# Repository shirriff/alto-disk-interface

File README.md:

# A Diablo disk emulator for use with a Xerox Alto

Note: This is still under development and is not working yet

The concept is a small box that you can plug into the Alto's disk interface, replacing the Diablo disk. The box will emulate the disk drive,
using a disk image from a SD card.

The hardware design is in the interface directory. It is based on a Teensy 4.1 microcontroller and uses a LCD touch screen as the user interface.

The driver software is in the TestApp directory.

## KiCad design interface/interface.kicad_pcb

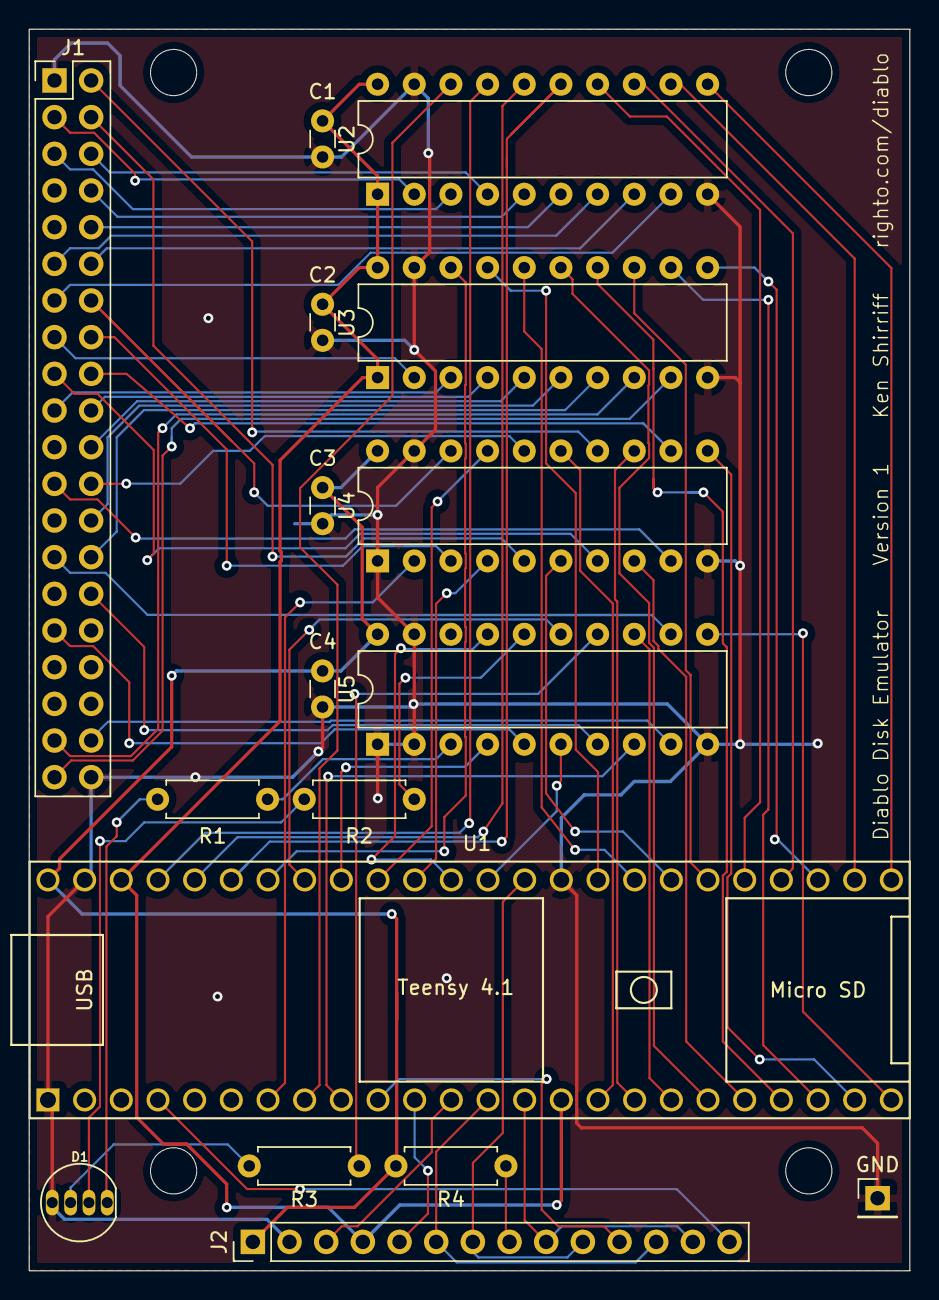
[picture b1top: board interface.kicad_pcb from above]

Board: 2 copper layers, 61.0 x 86.0 mm, 21 parts (0 on the bottom side), 76 nets.

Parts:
C1, C2, C3, C4: .1uF; C_Disc_D3.0mm_W1.6mm_P2.50mm
D1: LED_RGBC; LED-RGB-THRU
GND: TestPoint; Pin_Header_Straight_1x01_Pitch2.54mm
H1, H2, H3, H4: MountingHole; MountingHole_M3
J1: Conn_01x40_Female; connector-2x20
J2: Screen connector; Pin_Header_Straight_1x14_Pitch2.54mm
R1: 180; R_Axial_DIN0207_L6.3mm_D2.5mm_P7.62mm_Horizontal
R2, R3, R4: 100; R_Axial_DIN0207_L6.3mm_D2.5mm_P7.62mm_Horizontal
U1: Teensy4.1; Teensy41_simple
U2, U3: 74LVC245; DIP-20_W7.62mm
U4, U5: 74ACT240; DIP-20_W7.62mm

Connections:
/ADR_ACK: U1.39, U4.17
/CS: J2.3, U1.12
/CYL1: U1.42, U3.18
/CYL2: U1.44, U2.16
/CYL4: U1.33, U3.17
/CYL8: U1.22, U3.12
/CYL16: U1.29, U2.14
/CYL32: U1.25, U2.11
/CYL64: U1.43, U2.15
/CYL128: U1.26, U2.12
/DC: J2.5, U1.11
/DSK_ADR_ACK: J1.16, U4.3
/DSK_CYL1: J1.15, U3.2
/DSK_CYL2: J1.6, U2.4
/DSK_CYL4: J1.19, U3.3
/DSK_CYL8: J1.37, U3.8
/DSK_CYL16: J1.10, U2.6
/DSK_CYL32: J1.13, U2.9
/DSK_CYL64: J1.8, U2.5
/DSK_CYL128: J1.12, U2.8
/DSK_HEAD_SEL: J1.28, U3.7
/DSK_LAI: J1.18, U4.12
/DSK_RD_CLK: J1.2, U4.14
/DSK_RD_DATA: J1.38, U5.9
/DSK_RD_GATE: J1.39, U3.9
/DSK_READY: J1.31, U5.5
/DSK_RESTORE: J1.20, U3.4
/DSK_SECT1: J1.27, U5.12
/DSK_SECT2: J1.14, U4.18
/DSK_SECT4: J1.24, U4.16
/DSK_SECT8: J1.23, U4.9
/DSK_SECTOR: J1.30, U5.7
/DSK_SEEK_INCMP: J1.17, U4.7
/DSK_SEL1: J1.5, U2.3
/DSK_SEL4: J1.11, U2.7
/DSK_SRW: J1.4, U4.5
/DSK_STROBE: J1.22, U3.5
/DSK_WR_DATA: J1.3, U2.2
/DSK_WR_GATE: J1.26, U3.6
/GND: C1.2, C2.2, C3.2, C4.2, D1.4, GND.1, J1.1, J1.40, J2.2, U1.1, U1.34, U1.47, U2.10, U2.19, U3.10, U3.19, U4.1, U4.10, U4.19, U5.1, U5.2, U5.10, U5.19
/HEAD_SEL: U1.30, U3.13
/LAI: U1.20, U4.8
/LED: J2.8, R4.1
/LED_B: R3.2, U5.14
/LED_B_PWM: U1.36, U5.6
/LED_G: R2.2, U5.16
/LED_G_PWM: U1.40, U5.4
/LED_R: R1.2, U5.3
/LED_R_PWM: U1.37, U5.17
/RD_CLK: U1.31, U4.6
/RD_DATA: U1.24, U5.11
/RD_GATE: U1.27, U3.11
/READY: U1.41, U5.15
/RESTORE: U1.32, U3.16
/SCK: J2.7, J2.10, U1.35
/SDI: J2.6, J2.12, U1.13
/SDO: J2.9, J2.13, U1.14
/SECT1: U1.9, U5.8
/SECT2: U1.7, U4.2
/SECT4: U1.38, U4.4
/SECT8: U1.23, U4.11
/SECTOR: U1.18, U5.13
/SEEK_INCMP: U1.17, U4.13
/SEL1: U1.45, U2.17
/SEL4: U1.28, U2.13
/SRW: U1.16, U4.15
/STROBE: U1.19, U3.15
/T_CS: J2.11, U1.10
/T_IRQ: J2.14, U1.4
/VCC3: C1.1, C2.1, J2.4, U1.15, U1.46, U2.1, U2.20, U3.1, U3.20
/VCC5: C3.1, C4.1, J2.1, R4.2, U1.48, U4.20, U5.20
/WR_DATA: U1.8, U2.18
/WR_GATE: U1.21, U3.14
unnamed: D1.1, R1.1
unnamed: D1.2, R2.1
unnamed: D1.3, R3.1

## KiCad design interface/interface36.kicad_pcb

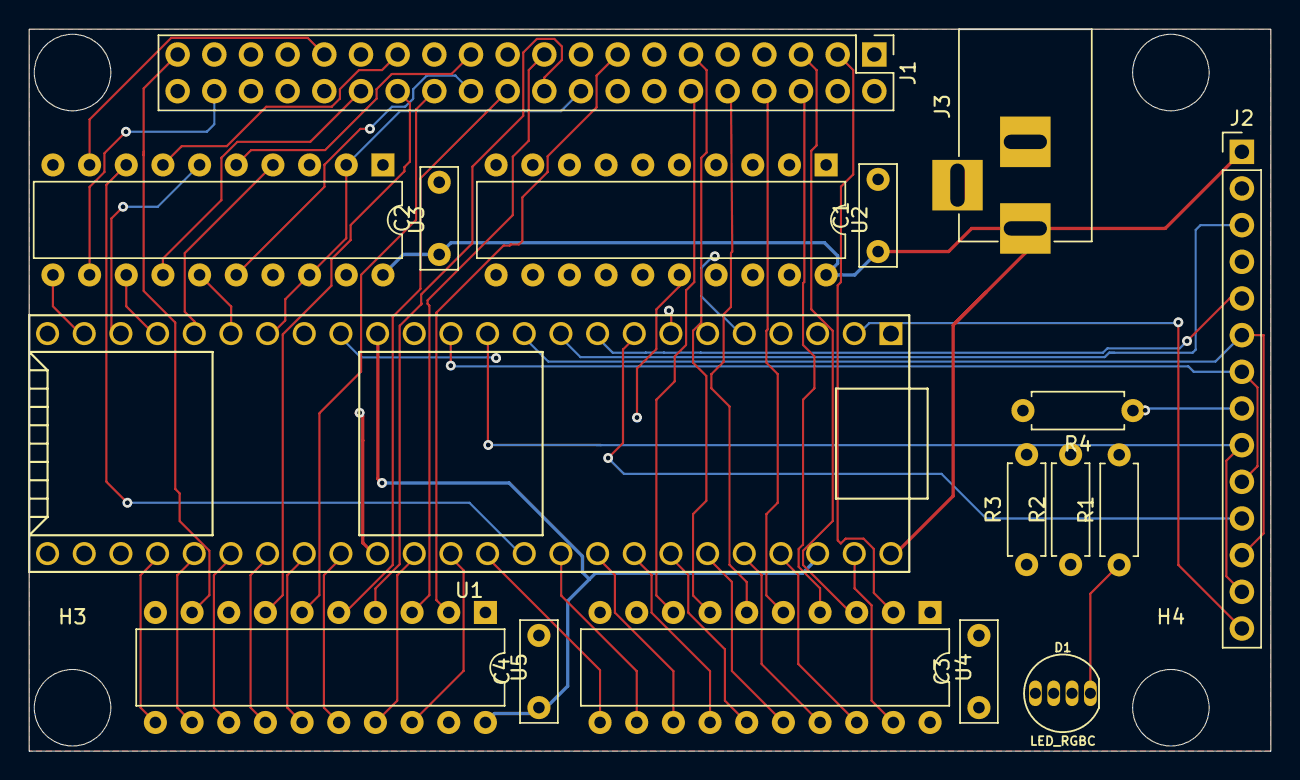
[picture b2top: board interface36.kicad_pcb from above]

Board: 2 copper layers, 86.0 x 50.0 mm, 21 parts (0 on the bottom side), 75 nets.

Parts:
C1, C2, C3, C4: .1uF; C_Rect_L7.0mm_W2.5mm_P5.00mm
D1: LED_RGBC; LED-RGB-THRU
H1, H2, H3, H4: MountingHole; MountingHole_5.3mm_M5
J1: Conn_01x40_Female; Pin_Header_Straight_2x20_Pitch2.54mm
J2: Conn_01x14_Female; Pin_Header_Straight_1x14_Pitch2.54mm
J3: Jack-DC; BARREL_JACK
R1: 180; R_Axial_DIN0207_L6.3mm_D2.5mm_P7.62mm_Horizontal
R2, R3, R4: 100; R_Axial_DIN0207_L6.3mm_D2.5mm_P7.62mm_Horizontal
U1: Teensy3.6; Teensy_36_simple
U2, U3: 74ACT240; DIP-20_W7.62mm
U4, U5: 74LVC245; DIP-20_W7.62mm

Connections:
/ADR_ACK: U1.16, U2.8
/CS: J2.3, U1.10
/CYL1: U1.39, U4.12
/CYL2: U1.42, U4.15
/CYL3: U1.37, U4.11
/CYL4: U1.41, U4.14
/CYL5: U1.29, U5.12
/CYL6: U1.35, U5.17
/CYL7: U1.43, U4.16
/CYL8: U1.36, U5.18
/DC: J2.5, U1.9
/DSK_ADR_ACK: J1.16, U2.12
/DSK_CYL1: J1.12, U4.8
/DSK_CYL2: J1.8, U4.5
/DSK_CYL3: J1.13, U4.9
/DSK_CYL4: J1.10, U4.6
/DSK_CYL5: J1.37, U5.8
/DSK_CYL6: J1.19, U5.3
/DSK_CYL7: J1.6, U4.4
/DSK_CYL8: J1.15, U5.2
/DSK_HEAD_SEL: J1.28, U5.7
/DSK_KSECT0: J1.23, U3.5
/DSK_KSECT1: J1.24, U3.16
/DSK_KSECT2: J1.14, U2.16
/DSK_KSECT3: J1.27, U3.7
/DSK_LAI: J1.18, U1.18, U3.2, U3.18
/DSK_RD_CLK: J1.2, U2.18
/DSK_RD_DATA: J1.38, U3.12
/DSK_RD_GATE: J1.39, U5.9
/DSK_READY: J1.31, U3.9
/DSK_RESTORE: J1.20, U5.4
/DSK_SECTOR: J1.30, U3.14
/DSK_SEEK_INCMP: J1.17, U2.9
/DSK_SEL1: J1.5, U4.3
/DSK_SEL4: J1.11, U4.7
/DSK_SRW: J1.4, U2.3
/DSK_STROBE: J1.22, U5.5
/DSK_WR_DATA: J1.3, U4.2
/DSK_WR_GATE: J1.26, U5.6
/GND: C1.2, C2.2, C3.2, C4.2, D1.4, J1.1, J1.40, J2.2, J3.2, U1.1, U1.34, U1.47, U2.1, U2.10, U2.19, U3.1, U3.10, U3.17, U3.19, U4.10, U4.19, U5.10, U5.19
/HEAD_SEL: U1.30, U5.13
/KSECT0: U1.19, U3.15
/KSECT1: U1.20, U3.4
/KSECT2: U1.7, U2.4
/KSECT3: U1.21, U3.13
/LED: J2.8, R4.1
/LED_B: R3.2, U2.7
/LED_B_PWM: U1.5, U2.13
/LED_G: R2.2, U2.14
/LED_G_PWM: U1.4, U2.6
/LED_R: R1.2, U2.5
/LED_R_PWM: U1.3, U2.15
/RD_CLK: U1.14, U2.2
/RD_DATA: U1.38, U3.8
/RD_GATE: U1.28, U5.11
/READY: U1.23, U3.11
/RESTORE: U1.33, U5.16
/SCK: J2.7, J2.10, U1.13
/SDI: J2.6, J2.12, U1.11
/SDO: J2.9, J2.13, U1.12
/SECTOR: U1.22, U3.6
/SEEK_INCMP: U1.17, U2.11
/SEL1: U1.44, U4.17
/SEL4: U1.40, U4.13
/SRW: U1.6, U2.17
/STROBE: U1.32, U5.15
/T_CS: J2.11, U1.8
/T_IRQ: J2.14, U1.2
/VCC3: C3.1, C4.1, J2.4, U1.15, U1.46, U4.1, U4.20, U5.1, U5.20
/VCC5: C1.1, C2.1, J2.1, J3.1, R4.2, U1.48, U2.20, U3.20
/WR_DATA: U1.45, U4.18
/WR_GATE: U1.31, U5.14
unnamed: D1.1, R1.1
unnamed: D1.2, R2.1
unnamed: D1.3, R3.1

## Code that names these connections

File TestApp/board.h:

// Outputs: note outputs are inverted
#define SECTOR 26
#define RD_CLK 39
#define RD_DATA 32
#define LAI 28
#define SRW 24
#define SEEK_INCMP 25
#define ADR_ACK 17
#define READY 19
#define SECT1 7
#define SECT2 5
#define SECT4 16
#define SECT8 31

#define LED_R 14 // Red and blue swapped
#define LED_B 15
#define LED_G 18

// Inputs
#define WR_DATA 6
#define SEL1 23
#define SEL4 36
#define CYL1 20
#define CYL2 22
#define CYL4 41
#define CYL8 30
#define CYL16 37
#define CYL32 33
#define CYL64 21
#define CYL128 34
#define RESTORE 40
#define STROBE 27
#define WR_GATE 29
#define RD_GATE 35
#define HEAD_SEL 38

// Outputs are active-low, but are driven through inverters.
// So writing a 1 pulls the board output low, which logically enables the signal.
#define OFF 0
#define ON 1

extern void setupBoard();
extern void loopBoard();
extern void stop(); // Infinite loop
#define BLACK 0x000000
#define RED 0xff0000
#define GREEN 0x00ff00
#define BLUE 0x0000ff
#define WHITE 0xC0ff60
#define MAGENTA 0x8000ff
#define YELLOW 0x80ff00
extern void led(long); // Light LED with specified color

extern void loadDisk(char *name);
extern void unloadDisk();

extern int debug; // flag
extern volatile int sectorCount;

extern void read();
extern void write();
extern void strobe();

// Insert N nops into the code.
// Inspired by https://github.com/tni/teensy-samples and https://stackoverflow.com/questions/26983548 and https://stackoverflow.com/questions/38484512
namespace {
template<size_t N> inline static void insertNops() {
    asm volatile ("nop");
    insertNops<N-1>();
}
template<> inline void insertNops<0>() {}
}

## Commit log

2025-07-22 Add schematic
2025-07-22 Various fixes
2025-07-22 Photo
